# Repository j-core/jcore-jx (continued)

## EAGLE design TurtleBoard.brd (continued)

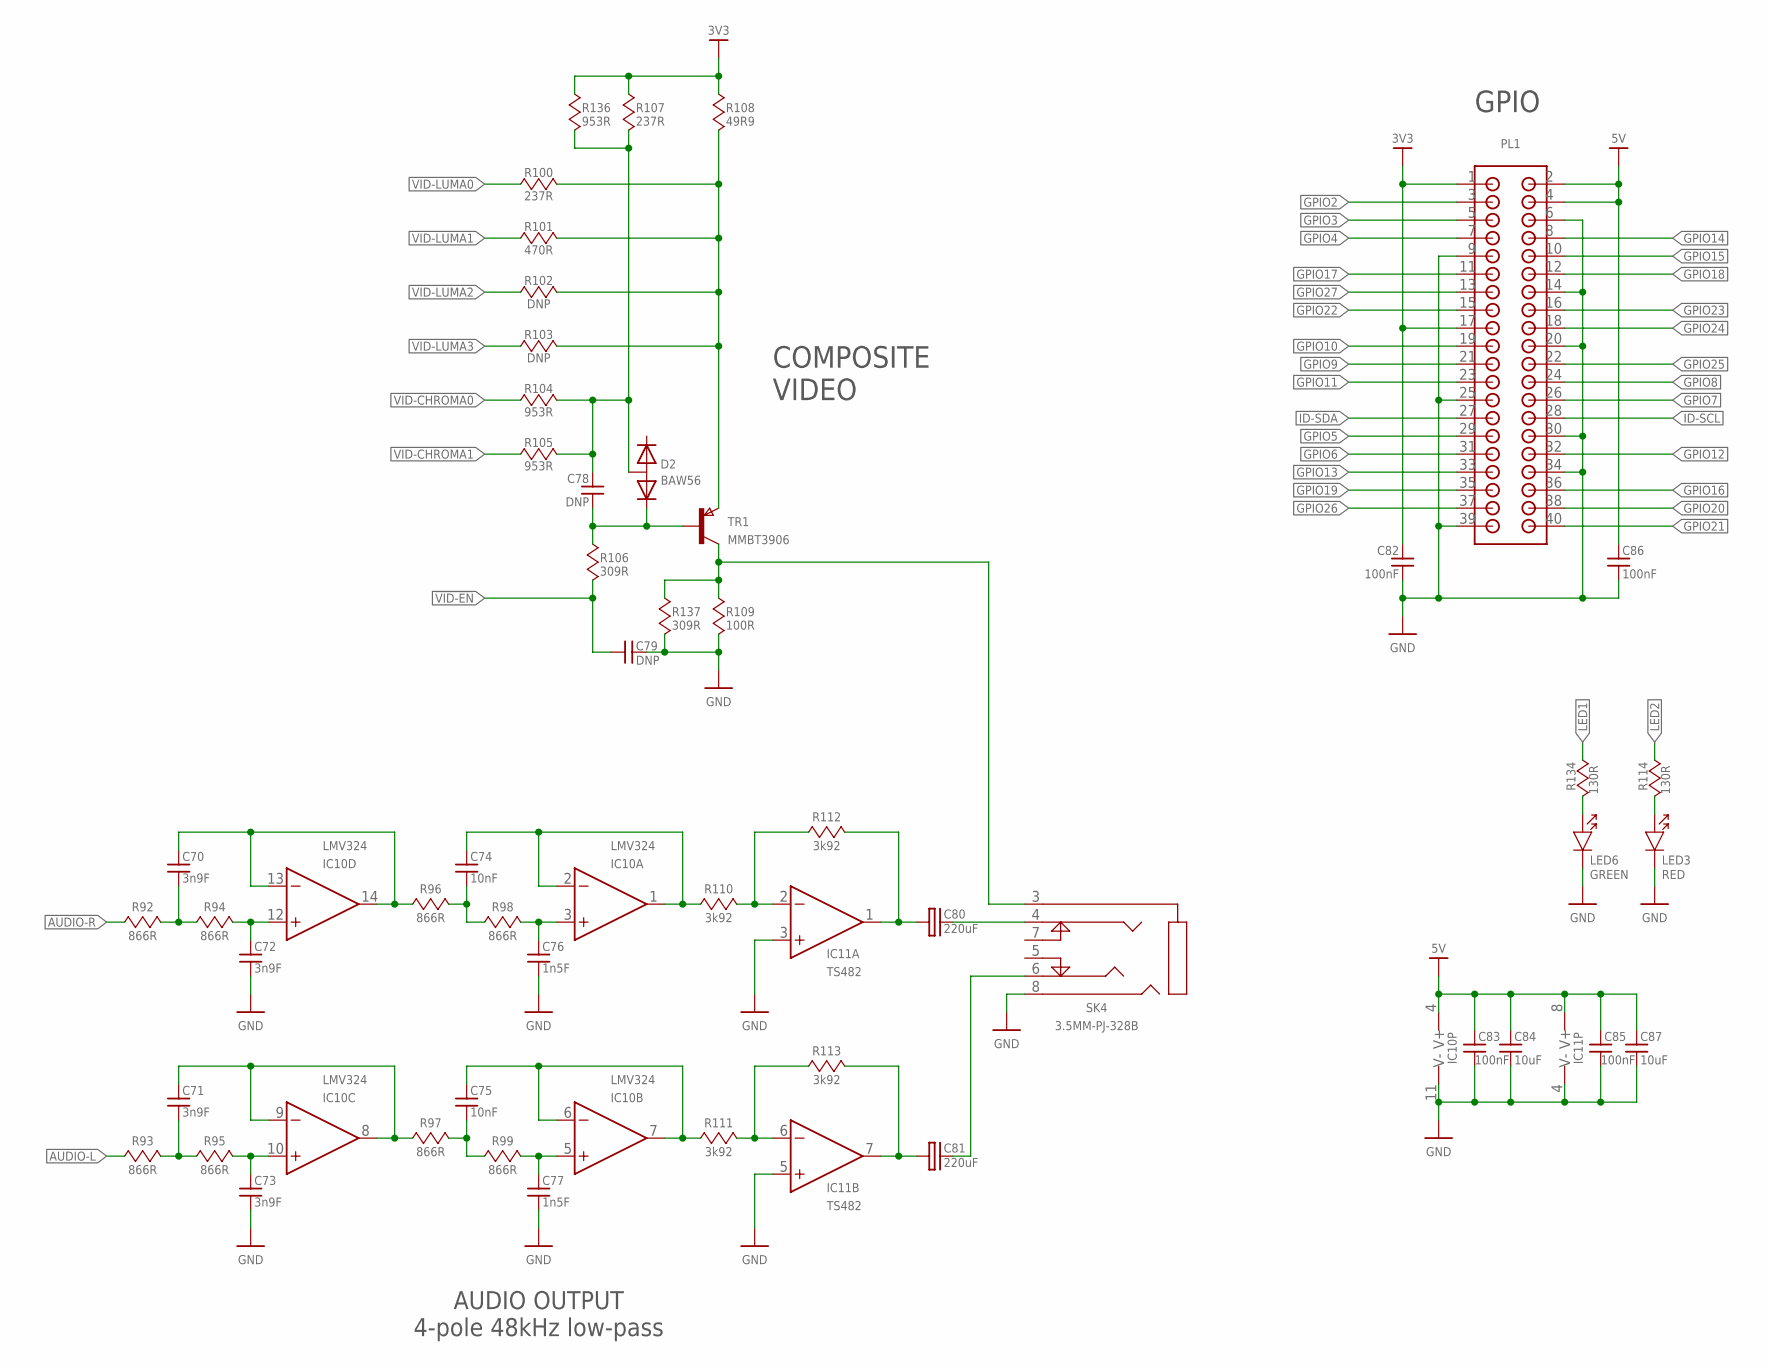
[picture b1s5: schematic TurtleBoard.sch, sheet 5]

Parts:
C70, C71, C72, C73: 3n9F; 0402
C74, C75: 10nF; 0402
C76, C77: 1n5F; 0402
C78, C79: DNP; 0402
C80, C81: 220uF; CP-6.3DIA
C82, C83, C85, C86: 100nF; 0402
C84, C87: 10uF; 0805
D2: BAW56; SC-75
IC10: LMV324; TSSOP14
IC11: TS482; MSOP08
LED3: RED; 0603-LED
LED6: GREEN; 0603-LED
PL1: 2X20-HEADER; 2X20_0.1"-HEADER
R92, R93, R94, R95, R96, R97, R98, R99: 866R; 0402
R100, R107: 237R; 0402
R101: 470R; 0402
R102, R103: DNP; 0402
R104, R105, R136: 953R; 0402
R106, R137: 309R; 0402
R108: 49R9; 0402
R109: 100R; 0402
R110, R111, R112, R113: 3k92; 0402
R114, R134: 130R; 0402
SK4: 3.5MM-PJ-328B
TR1: MMBT3906; SOT23

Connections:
3V3: C82.1, PL1.1, PL1.17, R107.2, R108.2, R136.2; also elsewhere on the board
5V: C83.2, C84.2, C85.2, C86.1, C87.2, IC10.4 (V+), IC11.8 (V+), PL1.2, PL1.4; also elsewhere on the board
!VID-EN: C79.1, R106.1; also elsewhere on the board
AUDIO-L: R93.1; also elsewhere on the board
AUDIO-R: R92.1; also elsewhere on the board
GND: C72.1, C73.1, C76.1, C77.1, C79.2, C82.2, C83.1, C84.1, C85.1, C86.2, C87.1, IC10.11 (V-), IC11.3 (+IN), IC11.4 (V-), IC11.5 (+IN), LED3.C, LED6.C, PL1.6, PL1.9, PL1.14, PL1.20, PL1.25, PL1.30, PL1.34, PL1.39, R109.1, R137.1, SK4.8; also elsewhere on the board
GPIO2: PL1.3; also elsewhere on the board
GPIO3: PL1.5; also elsewhere on the board
GPIO4: PL1.7; also elsewhere on the board
GPIO5: PL1.29; also elsewhere on the board
GPIO6: PL1.31; also elsewhere on the board
GPIO7: PL1.26; also elsewhere on the board
GPIO8: PL1.24; also elsewhere on the board
GPIO9: PL1.21; also elsewhere on the board
GPIO10: PL1.19; also elsewhere on the board
GPIO11: PL1.23; also elsewhere on the board
GPIO12: PL1.32; also elsewhere on the board
GPIO13: PL1.33; also elsewhere on the board
GPIO14: PL1.8; also elsewhere on the board
GPIO15: PL1.10; also elsewhere on the board
GPIO16: PL1.36; also elsewhere on the board
GPIO17: PL1.11; also elsewhere on the board
GPIO18: PL1.12; also elsewhere on the board
GPIO19: PL1.35; also elsewhere on the board
GPIO20: PL1.38; also elsewhere on the board
GPIO21: PL1.40; also elsewhere on the board
GPIO22: PL1.15; also elsewhere on the board
GPIO23: PL1.16; also elsewhere on the board
GPIO24: PL1.18; also elsewhere on the board
GPIO25: PL1.22; also elsewhere on the board
GPIO26: PL1.37; also elsewhere on the board
GPIO27: PL1.13; also elsewhere on the board
ID-SCL: PL1.28; also elsewhere on the board
ID-SDA: PL1.27; also elsewhere on the board
LED1: R134.2; also elsewhere on the board
LED2: R114.2; also elsewhere on the board
unnamed: IC11.2 (-IN), R110.2, R112.1
unnamed: C70.2, IC10.13 (-IN), IC10.14 (OUT), R96.1
unnamed: C70.1, R92.2, R94.1
unnamed: C72.2, IC10.12 (+IN), R94.2
unnamed: LED3.A, R114.1
unnamed: C80.- (MINUS), SK4.4
unnamed: C81.- (MINUS), SK4.6
unnamed: C78.1, D2.3 (A), R104.2, R105.2, R107.1, R136.1
unnamed: LED6.A, R134.1
unnamed: C78.2, D2.2 (K2), R106.2, TR1.1 (B)
unnamed: C74.2, IC10.1 (OUT), IC10.2 (-IN), R110.1
unnamed: C74.1, R96.2, R98.1
unnamed: C76.2, IC10.3 (+IN), R98.2
unnamed: C71.2, IC10.8 (OUT), IC10.9 (-IN), R97.1
unnamed: C80.+ (PLUS), IC11.1 (OUT), R112.2
unnamed: C71.1, R93.2, R95.1
unnamed: C73.2, IC10.10 (+IN), R95.2
unnamed: C75.2, IC10.6 (-IN), IC10.7 (OUT), R111.1
unnamed: C75.1, R97.2, R99.1
unnamed: C77.2, IC10.5 (+IN), R99.2
unnamed: IC11.6 (-IN), R111.2, R113.1
unnamed: C81.+ (PLUS), IC11.7 (OUT), R113.2
unnamed: R109.2, R137.2, SK4.3, TR1.3 (C)
unnamed: R100.2, R101.2, R102.2, R103.2, R108.1, TR1.2 (E)
VID-CHROMA0: R104.1; also elsewhere on the board
VID-CHROMA1: R105.1; also elsewhere on the board
VID-LUMA0: R100.1; also elsewhere on the board
VID-LUMA1: R101.1; also elsewhere on the board
VID-LUMA2: R102.1; also elsewhere on the board
VID-LUMA3: R103.1; also elsewhere on the board

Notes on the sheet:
GPIO
AUDIO OUTPUT 4-pole 48kHz low-pass
COMPOSITE VIDEO

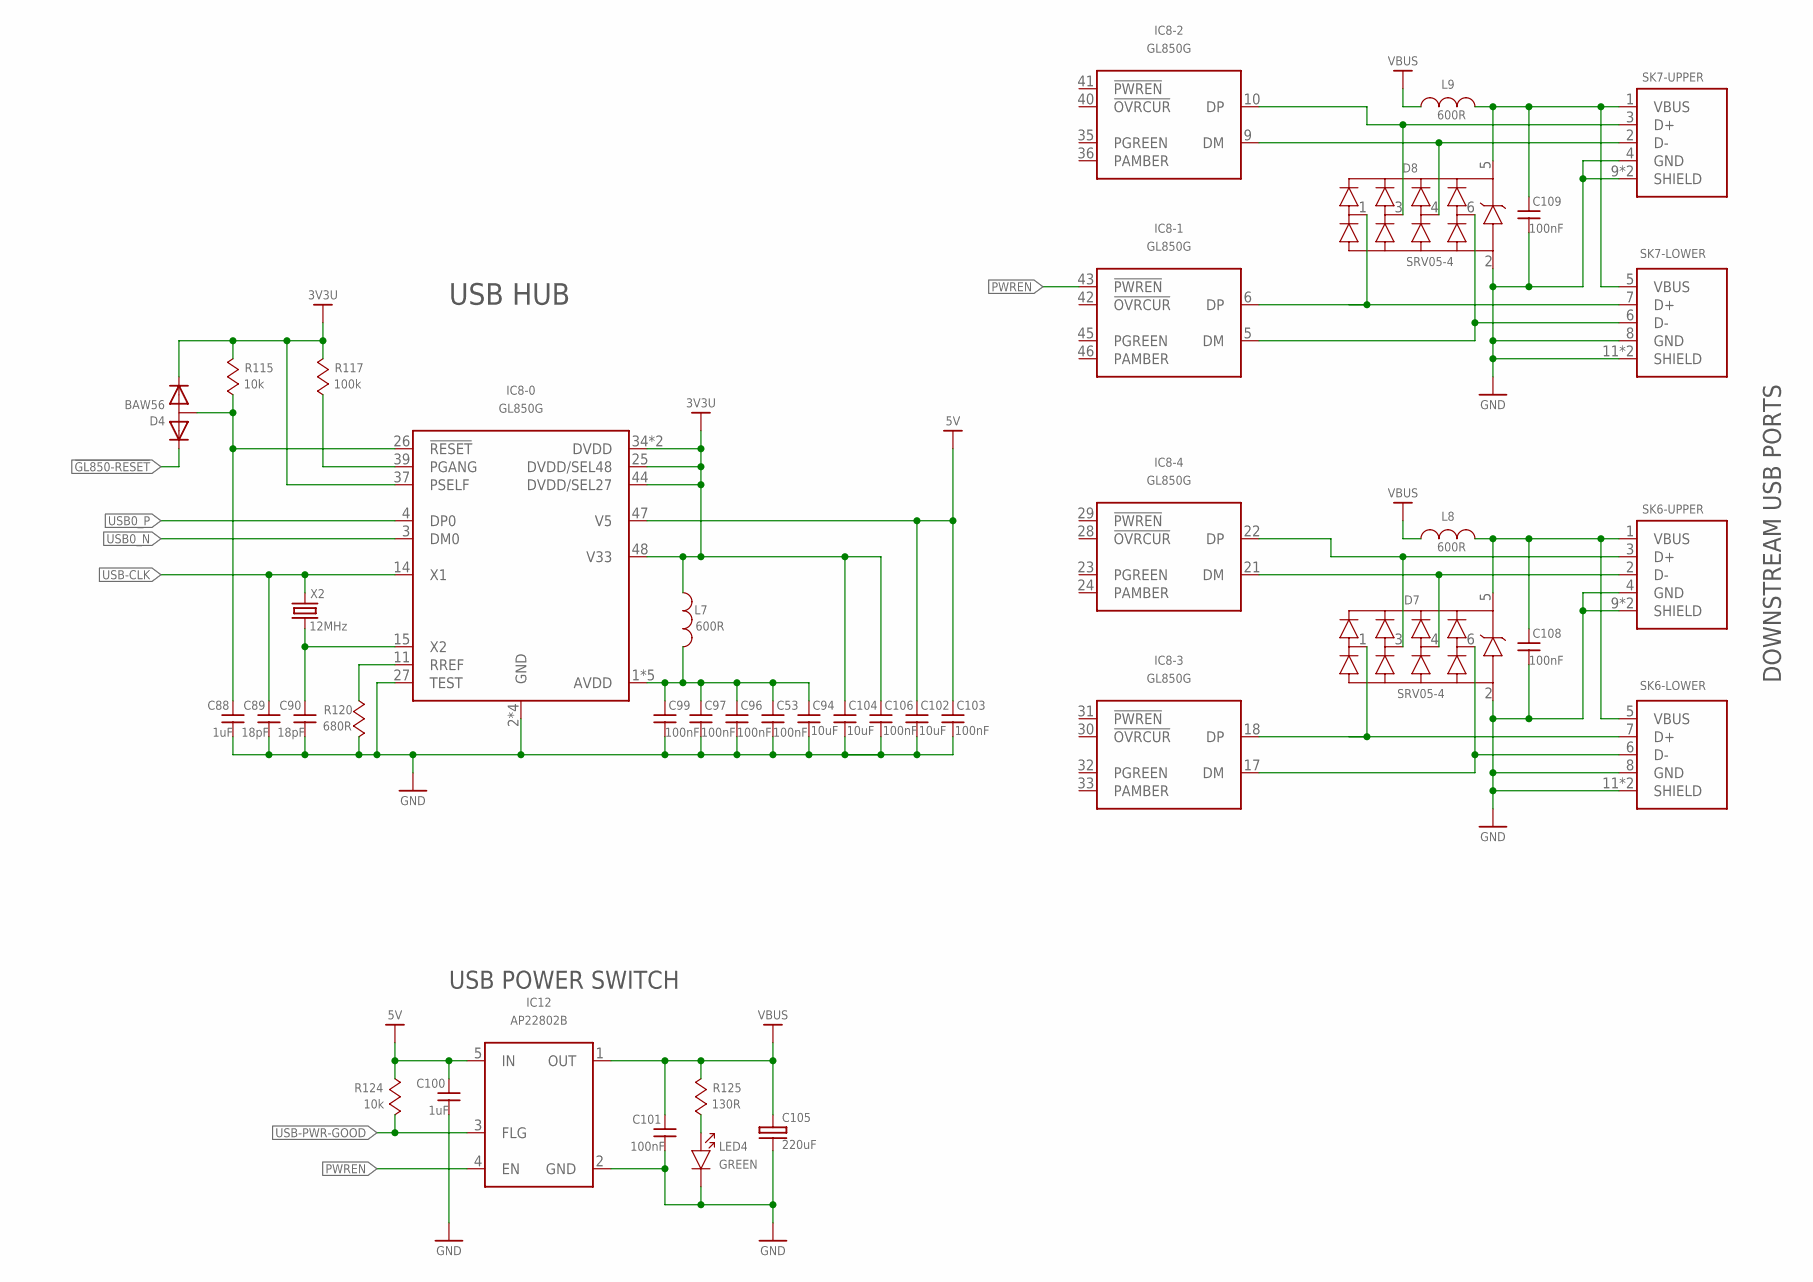
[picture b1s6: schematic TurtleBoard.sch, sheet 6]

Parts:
C53, C96, C97, C99, C101, C103, C106, C108, C109: 100nF; 0402
C88, C100: 1uF; 0402
C89, C90: 18pF; 0402
C94, C102, C104: 10uF; 0805
C105: 220uF; CP-6.3DIA
D4: BAW56; SC-75
D7, D8: SRV05-4; SOT23-6L
IC8: GL850G; LQFP48
IC12: AP22802B; SOT23-5
L7, L8, L9: 600R; C0805
LED4: GREEN; 0603-LED
R115, R124: 10k; 0402
R117: 100k; 0402
R120: 680R; 0402
R125: 130R; 0402
SK6, SK7: USB-A-DUAL
X2: 12MHz; XTAL-SMD-32X25

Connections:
3V3A: C53.2, C94.2, C96.2, C97.2, C99.2, IC8.1 (AVDD), IC8.7 (AVDD), IC8.12 (AVDD), IC8.16 (AVDD), IC8.19 (AVDD), L7.1
3V3U: C104.2, C106.2, D4.2 (K2), IC8.25 (DVDD/SEL48), IC8.34 (DVDD), IC8.37 (PSELF), IC8.38 (DVDD), IC8.44 (DVDD/SEL27), IC8.48 (V33), L7.2, R115.2, R117.2
5V: C100.2, C102.2, C103.2, IC8.47 (V5), IC12.5 (IN), R124.2; also elsewhere on the board
!GL850-RESET: D4.1 (K1); also elsewhere on the board
GND: C53.1, C88.1, C89.1, C90.1, C94.1, C96.1, C97.1, C99.1, C100.1, C101.1, C102.1, C103.1, C104.1, C105.- (MINUS), C106.1, C108.1, C109.1, D7.2 (-), D8.2 (-), IC8.2 (GND), IC8.8 (GND), IC8.13 (GND), IC8.20 (GND), IC8.27 (TEST), IC12.2 (GND), LED4.C, R120.1, SK6.4 (GND), SK6.8 (GND), SK6.9 (SHIELD), SK6.10 (SHIELD), SK6.11 (SHIELD), SK6.12 (SHIELD), SK7.4 (GND), SK7.8 (GND), SK7.9 (SHIELD), SK7.10 (SHIELD), SK7.11 (SHIELD), SK7.12 (SHIELD); also elsewhere on the board
unnamed: IC8.11 (RREF), R120.2
unnamed: IC8.39 (PGANG), R117.1
unnamed: C88.2, D4.3 (A), IC8.26 (!RESET), R115.1
unnamed: C108.2, D7.5 (+), L8.2, SK6.1 (VBUS), SK6.5 (VBUS)
unnamed: C109.2, D8.5 (+), L9.2, SK7.1 (VBUS), SK7.5 (VBUS)
unnamed: LED4.A, R125.1
PWREN: IC8.43 (!PWREN), IC12.4 (EN)
USB0_N: IC8.3 (DM0); also elsewhere on the board
USB0_P: IC8.4 (DP0); also elsewhere on the board
USB1_N: D7.4 (D3), IC8.21 (DM), SK6.2 (D-)
USB1_P: D7.3 (D2), IC8.22 (DP), SK6.3 (D+)
USB2_N: D7.6 (D4), IC8.17 (DM), SK6.6 (D-)
USB2_P: D7.1 (D1), IC8.18 (DP), SK6.7 (D+)
USB3_N: D8.4 (D3), IC8.9 (DM), SK7.2 (D-)
USB3_P: D8.3 (D2), IC8.10 (DP), SK7.3 (D+)
USB4_N: D8.6 (D4), IC8.5 (DM), SK7.6 (D-)
USB4_P: D8.1 (D1), IC8.6 (DP), SK7.7 (D+)
USB-CLK: C89.2, IC8.14 (X1), X2.3 (2); also elsewhere on the board
USB-CLK2: C90.2, IC8.15 (X2), X2.1
USB-PWR-GOOD: IC12.3 (FLG), R124.1; also elsewhere on the board
VBUS: C101.2, C105.+ (PLUS), IC12.1 (OUT), L8.1, L9.1, R125.2

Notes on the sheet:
USB HUB
DOWNSTREAM USB PORTS
USB POWER SWITCH

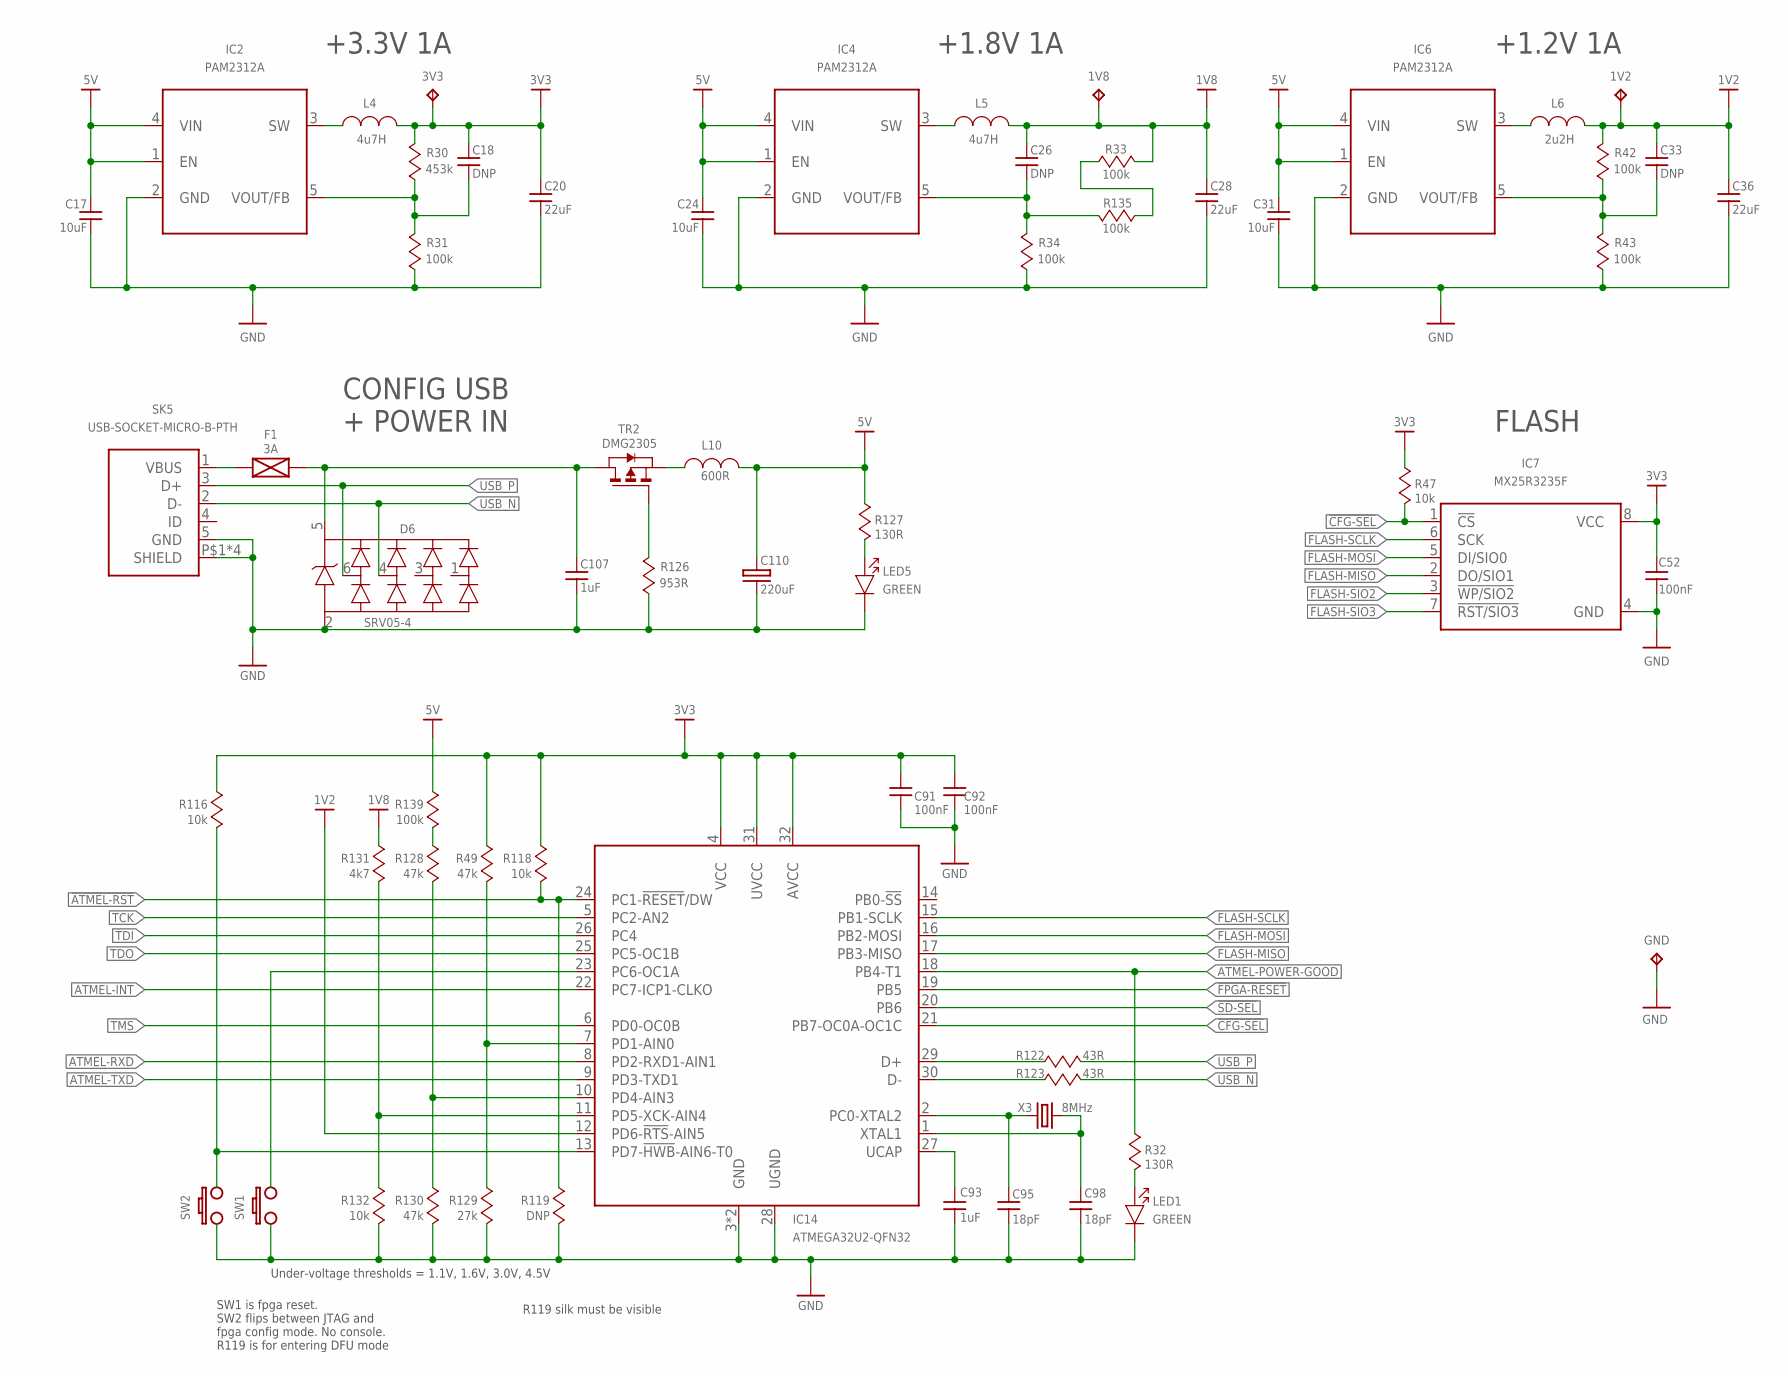
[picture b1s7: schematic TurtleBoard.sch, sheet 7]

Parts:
C17, C24, C31: 10uF; 0805
C18, C26, C33: DNP; 0402
C20, C28, C36: 22uF; 0805
C52, C91, C92: 100nF; 0402
C93, C107: 1uF; 0402
C95, C98: 18pF; 0402
C110: 220uF; CP-6.3DIA
D6: SRV05-4; SOT23-6L
F1: 3A; C1812
IC2, IC4, IC6: PAM2312A; TSOT23-5
IC7: MX25R3235F; SOIJ-8
IC14: ATMEGA32U2-QFN32; QFN-32
L4, L5: 4u7H; SRN6045
L6: 2u2H; SRN6045
L10: 600R; C1210
LED1, LED5: GREEN; 0603-LED
R30: 453k; 0402
R31, R33, R34, R42, R43, R135, R139: 100k; 0402
R32, R127: 130R; 0402
R47, R116, R118, R132: 10k; 0402
R49, R128, R130: 47k; 0402
R119: DNP; 0603
R122, R123: 43R; 0402
R126: 953R; 0402
R129: 27k; 0402
R131: 4k7; 0402
SK5: USB-SOCKET-MICRO-B-PTH; USB-MICRO-B-PTH
SW1, SW2: SWITCH-SPSTTACT-6X3; TACT-6X3
TP1: 3V3; P1-10
TP2: 1V8; P1-10
TP3: GND; P1-10
TP4: 1V2; P1-10
TR2: DMG2305; SOT23
X3: 8MHz; CRYSTAL-ABM3

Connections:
1V2: C33.1, C36.2, IC14.12 (PD6-!RTS!-AIN5), L6.2, R42.2, TP4.1; also elsewhere on the board
1V8: C26.1, C28.2, L5.2, R33.2, R131.2, TP2.1; also elsewhere on the board
3V3: C18.1, C20.2, C91.2, C92.2, IC14.4 (VCC), IC14.31 (UVCC), IC14.32 (AVCC), L4.2, R30.2, R47.2, R49.2, R116.2, R118.2, TP1.1; also elsewhere on the board
5V: C17.2, C24.2, C31.2, C110.+ (PLUS), IC2.1 (EN), IC2.4 (VIN), IC4.1 (EN), IC4.4 (VIN), IC6.1 (EN), IC6.4 (VIN), L10.2, R127.2, R139.2; also elsewhere on the board
!ATMEL-RST: IC14.24 (PC1-!RESET!/DW), R118.1, R119.2; also elsewhere on the board
!CFG-SEL: IC7.1 (!CS), IC14.21 (PB7-OC0A-OC1C), R47.1; also elsewhere on the board
!FPGA-RESET: IC14.19 (PB5); also elsewhere on the board
!SD-SEL: IC14.20 (PB6); also elsewhere on the board
ATMEL-INT: IC14.22 (PC7-ICP1-CLKO); also elsewhere on the board
ATMEL-POWER-GOOD: IC14.18 (PB4-T1), R32.2; also elsewhere on the board
ATMEL-RXD: IC14.8 (PD2-RXD1-AIN1); also elsewhere on the board
ATMEL-TXD: IC14.9 (PD3-TXD1); also elsewhere on the board
FLASH-MISO: IC7.2 (DO/SIO1), IC14.17 (PB3-MISO); also elsewhere on the board
FLASH-MOSI: IC7.5 (DI/SIO0), IC14.16 (PB2-MOSI); also elsewhere on the board
FLASH-SCLK: IC7.6 (SCK), IC14.15 (PB1-SCLK); also elsewhere on the board
FLASH-SIO2: IC7.3 (!WP/SIO2); also elsewhere on the board
FLASH-SIO3: IC7.7 (!RST/SIO3); also elsewhere on the board
GND: C17.1, C20.1, C24.1, C28.1, C31.1, C36.1, C52.1, C91.1, C92.1, C93.1, C95.1, C98.1, C107.2, C110.- (MINUS), D6.2 (-), IC2.2 (GND), IC4.2 (GND), IC6.2 (GND), IC7.4 (GND), IC14.3 (GND), IC14.28 (UGND), IC14.P (GND), LED1.C, LED5.C, R31.1, R34.1, R43.1, R119.1, R126.1, R129.1, R130.1, R132.1, SK5.5 (GND), SK5.P$1 (SHIELD), SK5.P$2 (SHIELD), SK5.P$3 (SHIELD), SK5.P$4 (SHIELD), SW1.P$2 (2), SW2.P$2 (2), TP3.1; also elsewhere on the board
unnamed: LED1.A, R32.1
unnamed: C93.2, IC14.27 (UCAP)
unnamed: IC14.29 (D+), R122.1
unnamed: IC14.30 (D-), R123.1
unnamed: C107.1, D6.5 (+), F1.1, TR2.3 (D)
unnamed: F1.2, SK5.1 (VBUS)
unnamed: IC2.3 (SW), L4.1
unnamed: IC6.3 (SW), L6.1
unnamed: C33.2, IC6.5 (VOUT/FB), R42.1, R43.2
unnamed: C18.2, IC2.5 (VOUT/FB), R30.1, R31.2
unnamed: R126.2, TR2.1 (G)
unnamed: LED5.A, R127.1
unnamed: IC14.13 (PD7-!HWB!-AIN6-T0), R116.1, SW2.P$1 (1)
unnamed: C98.2, IC14.1 (XTAL1), X3.2
unnamed: C95.2, IC14.2 (PC0-XTAL2), X3.1
unnamed: IC14.10 (PD4-AIN3), R128.1, R130.2
unnamed: R33.1, R135.1
unnamed: IC4.3 (SW), L5.1
unnamed: C26.2, IC4.5 (VOUT/FB), R34.2, R135.2
unnamed: L10.1, TR2.2 (S)
unnamed: IC14.7 (PD1-AIN0), R49.1, R129.2
unnamed: IC14.23 (PC6-OC1A), SW1.P$1 (1)
unnamed: IC14.11 (PD5-XCK-AIN4), R131.1, R132.2
unnamed: R128.2, R139.1
TCK: IC14.5 (PC2-AN2); also elsewhere on the board
TDI: IC14.26 (PC4); also elsewhere on the board
TDO: IC14.25 (PC5-OC1B); also elsewhere on the board
TMS: IC14.6 (PD0-OC0B); also elsewhere on the board
USB_N: D6.4 (D3), R123.2, SK5.2 (D-)
USB_P: D6.6 (D4), R122.2, SK5.3 (D+)
V: C52.2, IC7.8 (VCC)

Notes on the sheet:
SW1 is fpga reset. SW2 flips between JTAG and fpga config mode. No console. R119 is for entering DFU mode
Under-voltage thresholds = 1.1V, 1.6V, 3.0V, 4.5V
FLASH
+1.2V 1A
+3.3V 1A
+1.8V 1A
CONFIG USB + POWER IN
R119 silk must be visible

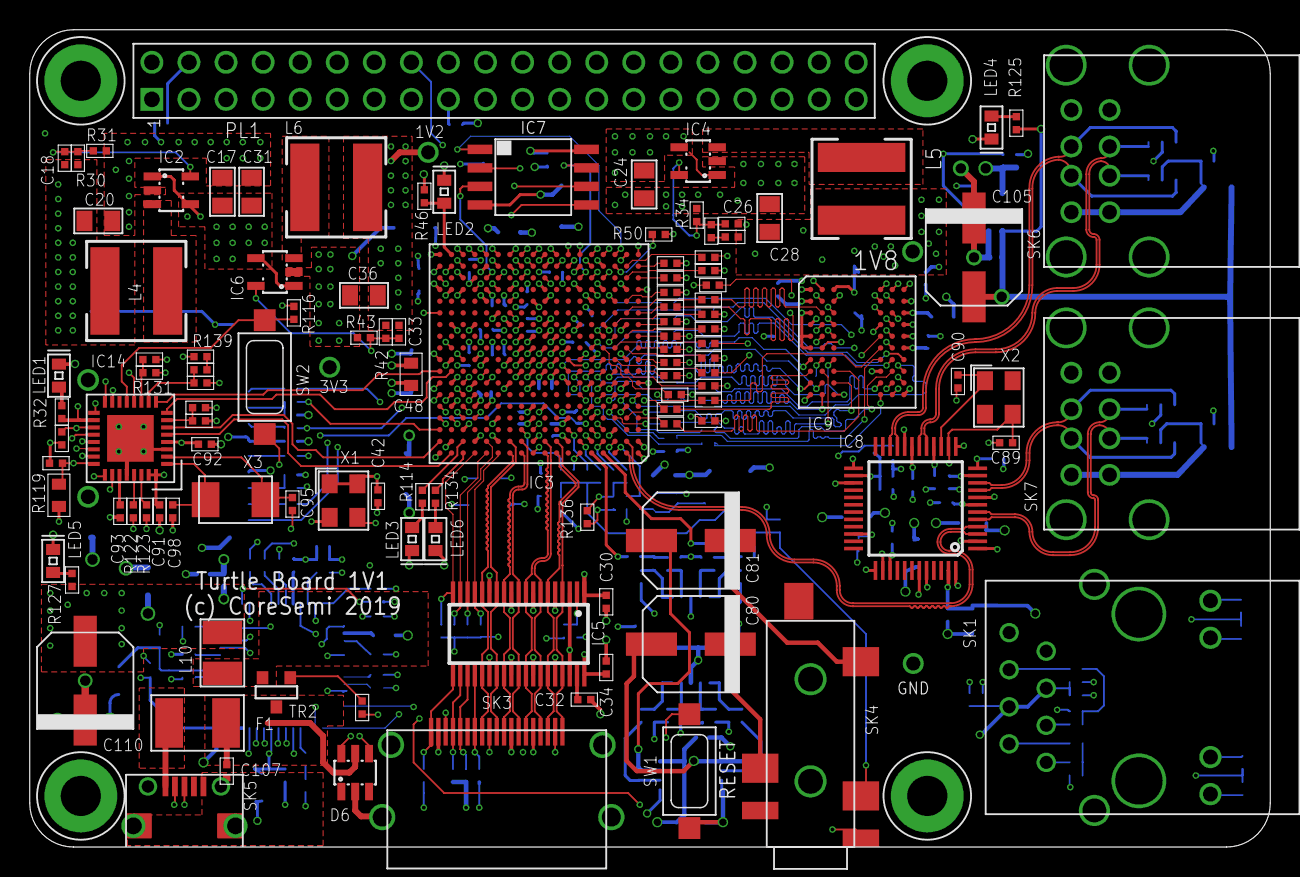
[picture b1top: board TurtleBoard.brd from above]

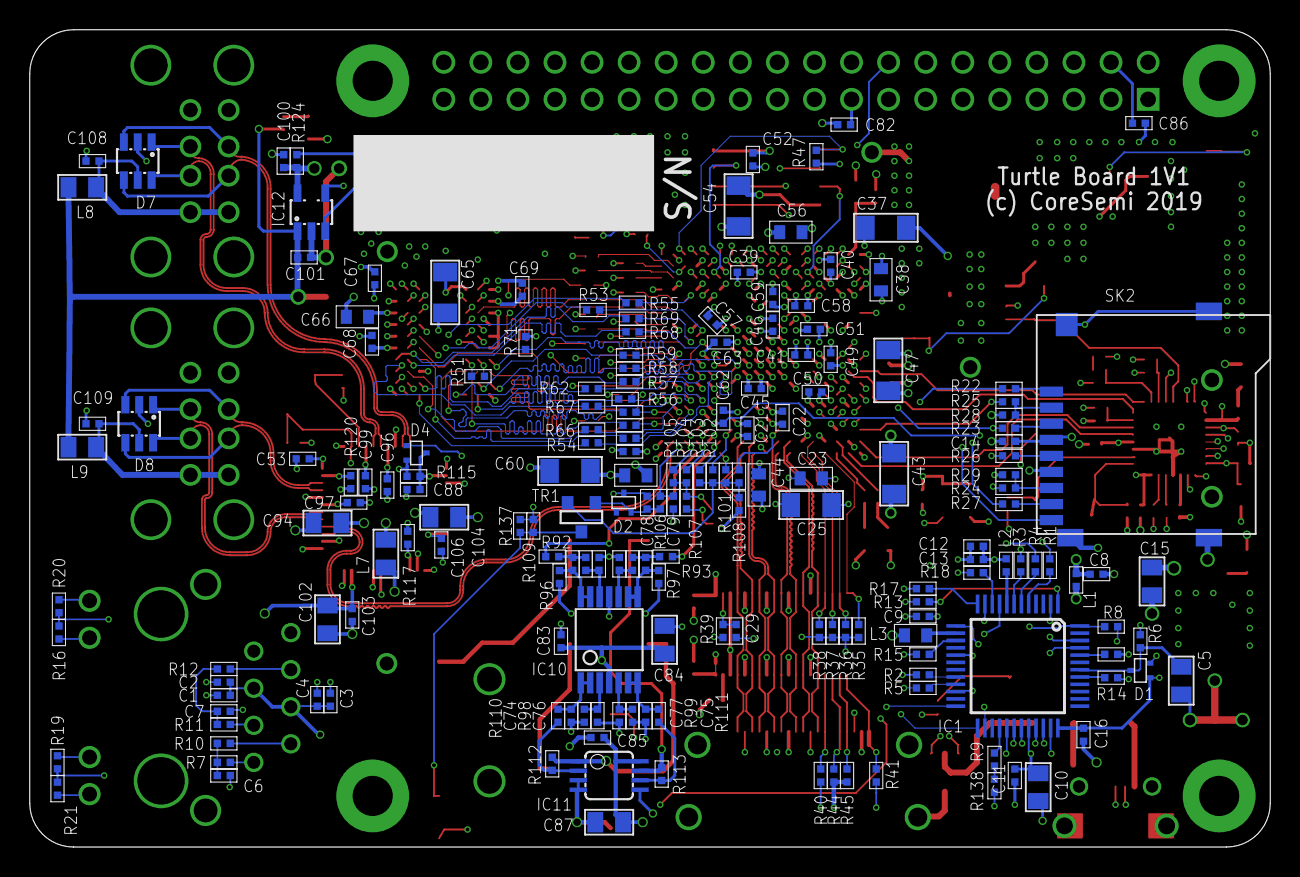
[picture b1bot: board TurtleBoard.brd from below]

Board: 8 copper layers, 85.0 x 56.0 mm, 303 parts (182 on the bottom side), 288 nets.

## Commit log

2020-05-18 SEI 2016 1v0 platform board
2020-05-18 Schematic and top silk pdf files
2020-05-18 schamtic 1v1 board, as built
2020-06-21 v1.1 As built, Q3 2019
